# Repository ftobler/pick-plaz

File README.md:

# pick-plaz
Open source pick and place machine

[CAD Onshape](https://cad.onshape.com/documents/175bb45940c329c46a77df39/w/56e16a8885c2fef63520b9e2/e/e7ab10496d879b6cf281b14f)

[STEP file repostory (CAD)](https://github.com/ftobler/pick-plaz-cad)

[More Pictures (Imgur)](https://imgur.com/a/lOQ79OQ)

## Issues

* Part preview missing zero point of ICs

# Wishlist

* Camera sharpen menu in UI (laplacian of camera image)

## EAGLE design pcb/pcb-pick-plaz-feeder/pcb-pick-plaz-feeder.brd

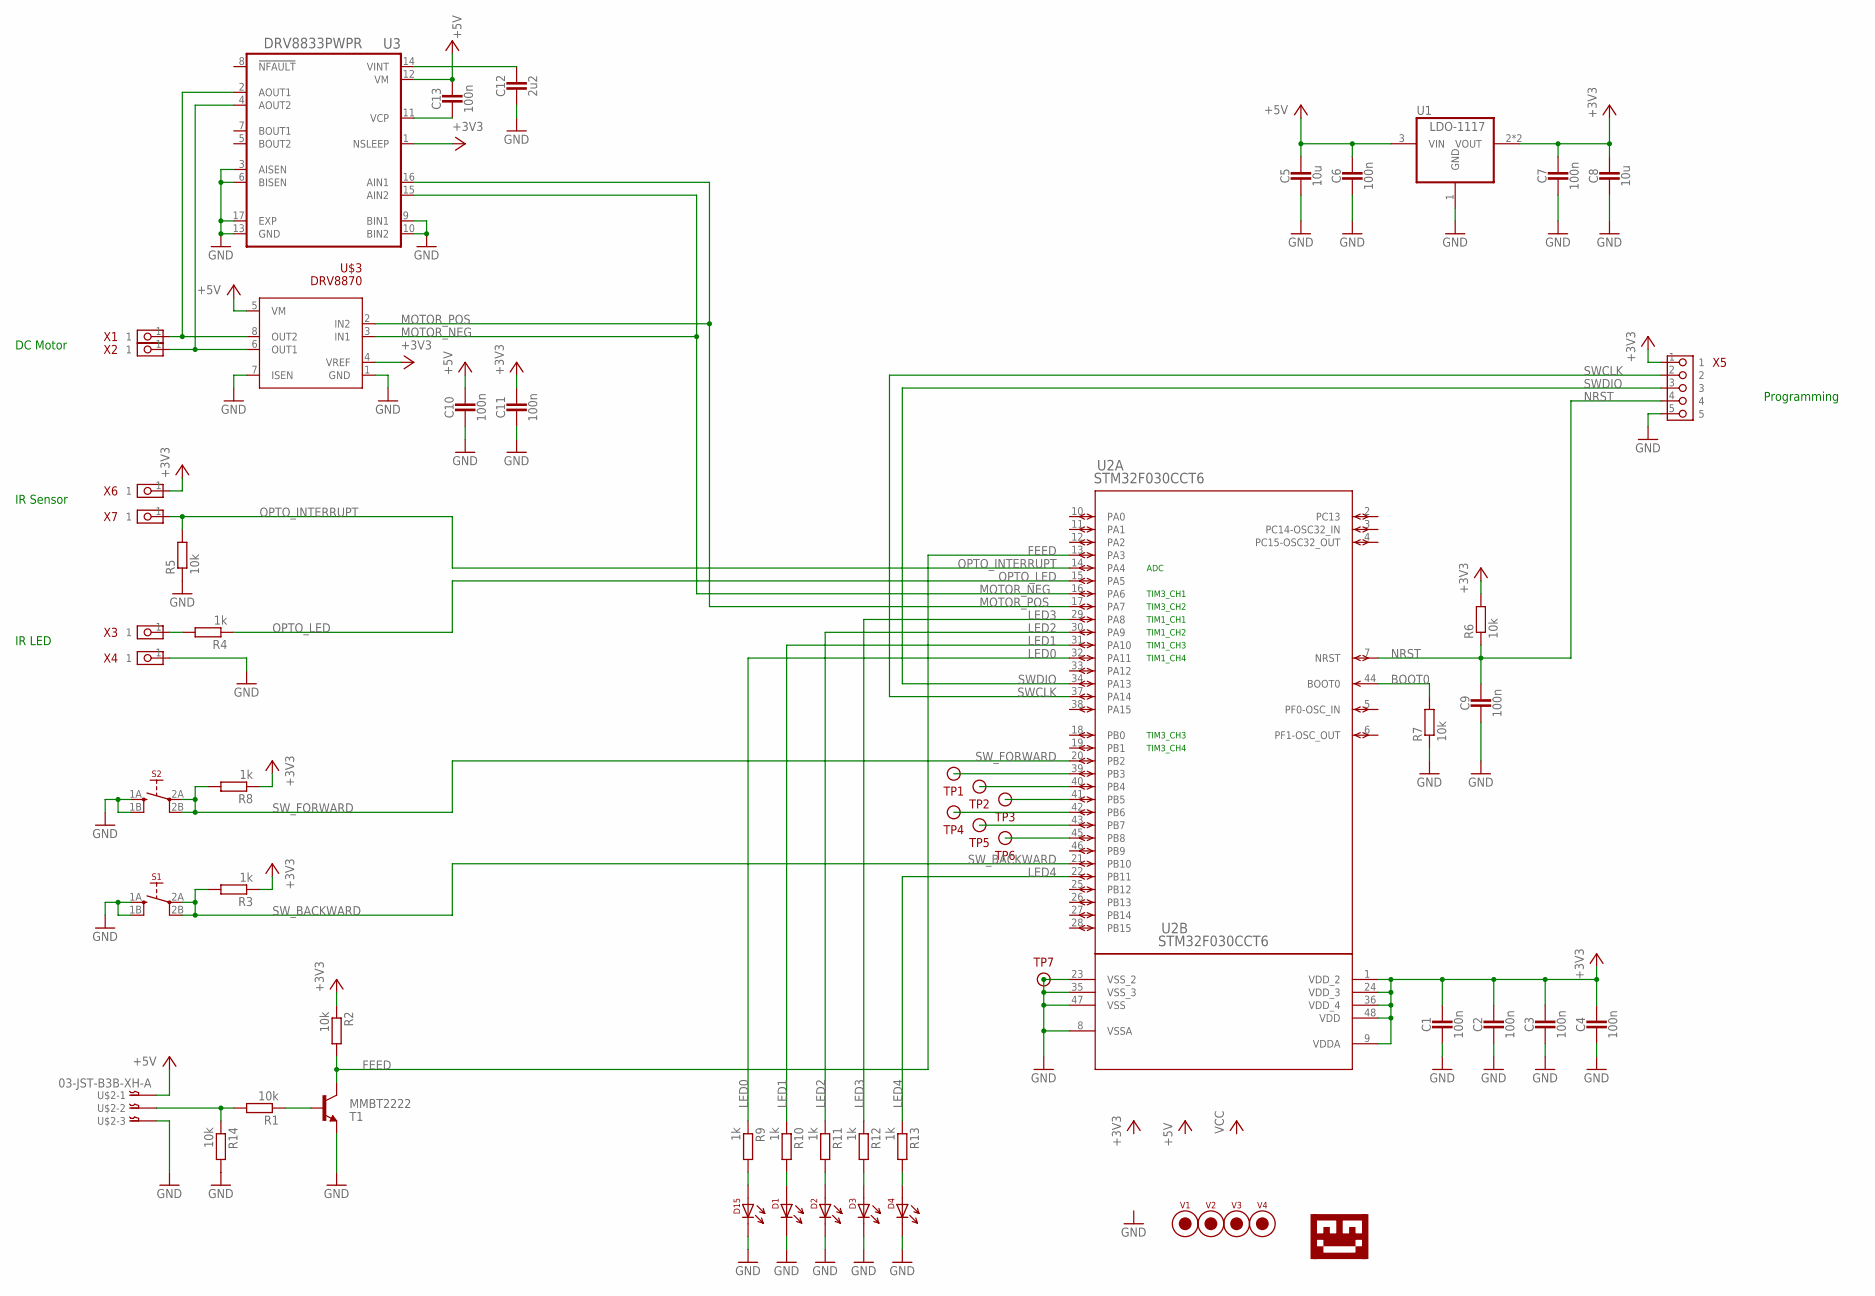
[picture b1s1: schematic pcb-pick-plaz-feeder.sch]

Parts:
C1, C2, C3, C4, C6, C7, C9, C10, C11, C13: 100n; 0603_CAP
C5, C8: 10u; 0805_CAP
C12: 2u2; 0805_CAP
D1, D2, D3, D4, D15: LED-0805; 0805-DOT
R1, R2, R5, R6, R7, R14: 10k; 0603-RES
R3, R4, R8, R9, R10, R11, R12, R13: 1k; 0603-RES
S1, S2: SWITCH_2PD; SWITCH_WH
T1: MMBT2222; SOT23-BEC
TP1, TP2, TP3, TP4, TP5, TP6, TP7: TESTPIN; PIN-SMD-1X1-TEST_1M5
U1: LDO-1117; SOT-89
U2: STM32F030CCT6; LQFP48-7X7MM
U3: DRV8833PWPR; IC_DRV8833PWPR
U$1: LOGO-TOBENG-1MM-FINISH; TOBENG-1MM-FINISH
U$2: 03-JST-B3B-XH-A; B3B-XH
U$3: DRV8870; SOIC-8
V1, V2, V3, V4: FIDUCIAL2MM; FIDUCIAL_2MM
X1, X2, X3, X4, X6, X7: PIN_1X1SMD_BIG_L; PIN_1X1_SMD_BIG_L
X5: PIN_5X1HD; PIN_5X1_HD

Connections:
+3V3: C1.1, C2.1, C3.1, C4.1, C7.1, C8.P$1 (1), C11.1, R2.1, R3.1, R6.2, R8.1, U1.2 (VOUT), U1.2@1 (VOUT), U2.1 (VDD_2), U2.9 (VDDA), U2.24 (VDD_3), U2.36 (VDD_4), U2.48 (VDD), U3.1 (NSLEEP), U$3.4 (VREF), X5.1, X6.1
+5V: C5.P$1 (1), C6.1, C10.1, C13.1, U1.3 (VIN), U3.12 (VM), U$2.P$1, U$3.5 (VM)
BOOT0: R7.2, U2.44 (BOOT0)
FEED: R2.2, T1.C, U2.13 (PA3)
GND: C1.2, C2.2, C3.2, C4.2, C5.P$2 (2), C6.2, C7.2, C8.P$2 (2), C9.2, C10.2, C11.2, C12.P$2 (2), D1.2, D2.2, D3.2, D4.2, D15.2, R5.1, R7.1, R14.2, S1.1A (1), S1.1B (2), S2.1A (1), S2.1B (2), T1.E, TP7.1, U1.1 (GND), U2.8 (VSSA), U2.23 (VSS_2), U2.35 (VSS_3), U2.47 (VSS), U3.3 (AISEN), U3.6 (BISEN), U3.9 (BIN1), U3.10 (BIN2), U3.13 (GND), U3.17 (EXP), U$2.P$3, U$3.1 (GND), U$3.7 (ISEN), X4.1, X5.5
LED0: R9.1, U2.32 (PA11)
LED1: R10.1, U2.31 (PA10)
LED2: R11.1, U2.30 (PA9)
LED3: R12.1, U2.29 (PA8)
LED4: R13.1, U2.22 (PB11)
MOTOR_NEG: U2.16 (PA6), U3.15 (AIN2), U$3.3 (IN1)
MOTOR_POS: U2.17 (PA7), U3.16 (AIN1), U$3.2 (IN2)
unnamed: U3.4 (AOUT2), U$3.6 (OUT1), X2.1
unnamed: U3.2 (AOUT1), U$3.8 (OUT2), X1.1
unnamed: R1.2, R14.1, U$2.P$2
unnamed: R1.1, T1.B
unnamed: R4.2, X3.1
unnamed: D15.1, R9.2
unnamed: D1.1, R10.2
unnamed: D2.1, R11.2
unnamed: D3.1, R12.2
unnamed: D4.1, R13.2
unnamed: TP1.1, U2.39 (PB3)
unnamed: TP2.1, U2.40 (PB4)
unnamed: TP3.1, U2.41 (PB5)
unnamed: TP4.1, U2.42 (PB6)
unnamed: TP5.1, U2.43 (PB7)
unnamed: TP6.1, U2.45 (PB8)
unnamed: C12.P$1 (1), U3.14 (VINT)
unnamed: C13.2, U3.11 (VCP)
NRST: C9.1, R6.1, U2.7 (NRST), X5.4
OPTO_INTERRUPT: R5.2, U2.14 (PA4), X7.1
OPTO_LED: R4.1, U2.15 (PA5)
SWCLK: U2.37 (PA14), X5.2
SWDIO: U2.34 (PA13), X5.3
SW_BACKWARD: R3.2, S1.2A (3), S1.2B (4), U2.21 (PB10)
SW_FORWARD: R8.2, S2.2A (3), S2.2B (4), U2.20 (PB2)

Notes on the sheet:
Programming
DC Motor
IR LED
IR Sensor
ADC
TIM1_CH1
TIM1_CH2
TIM3_CH1
TIM3_CH2
TIM3_CH3
TIM3_CH4
TIM1_CH3
TIM1_CH4

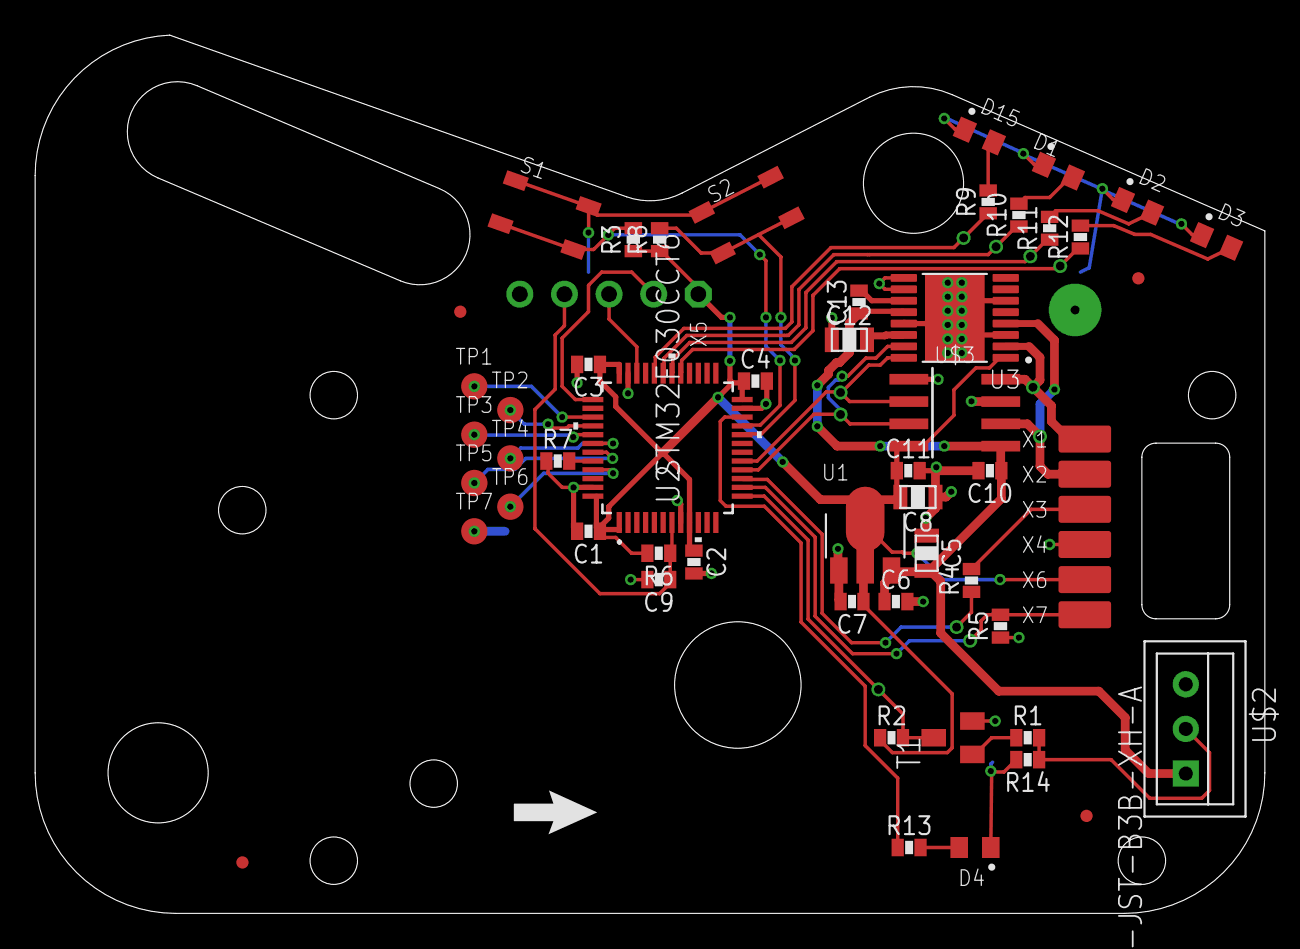
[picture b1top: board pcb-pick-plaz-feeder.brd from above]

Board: 2 copper layers, 70.0 x 50.0 mm, 59 parts (0 on the bottom side), 37 nets.

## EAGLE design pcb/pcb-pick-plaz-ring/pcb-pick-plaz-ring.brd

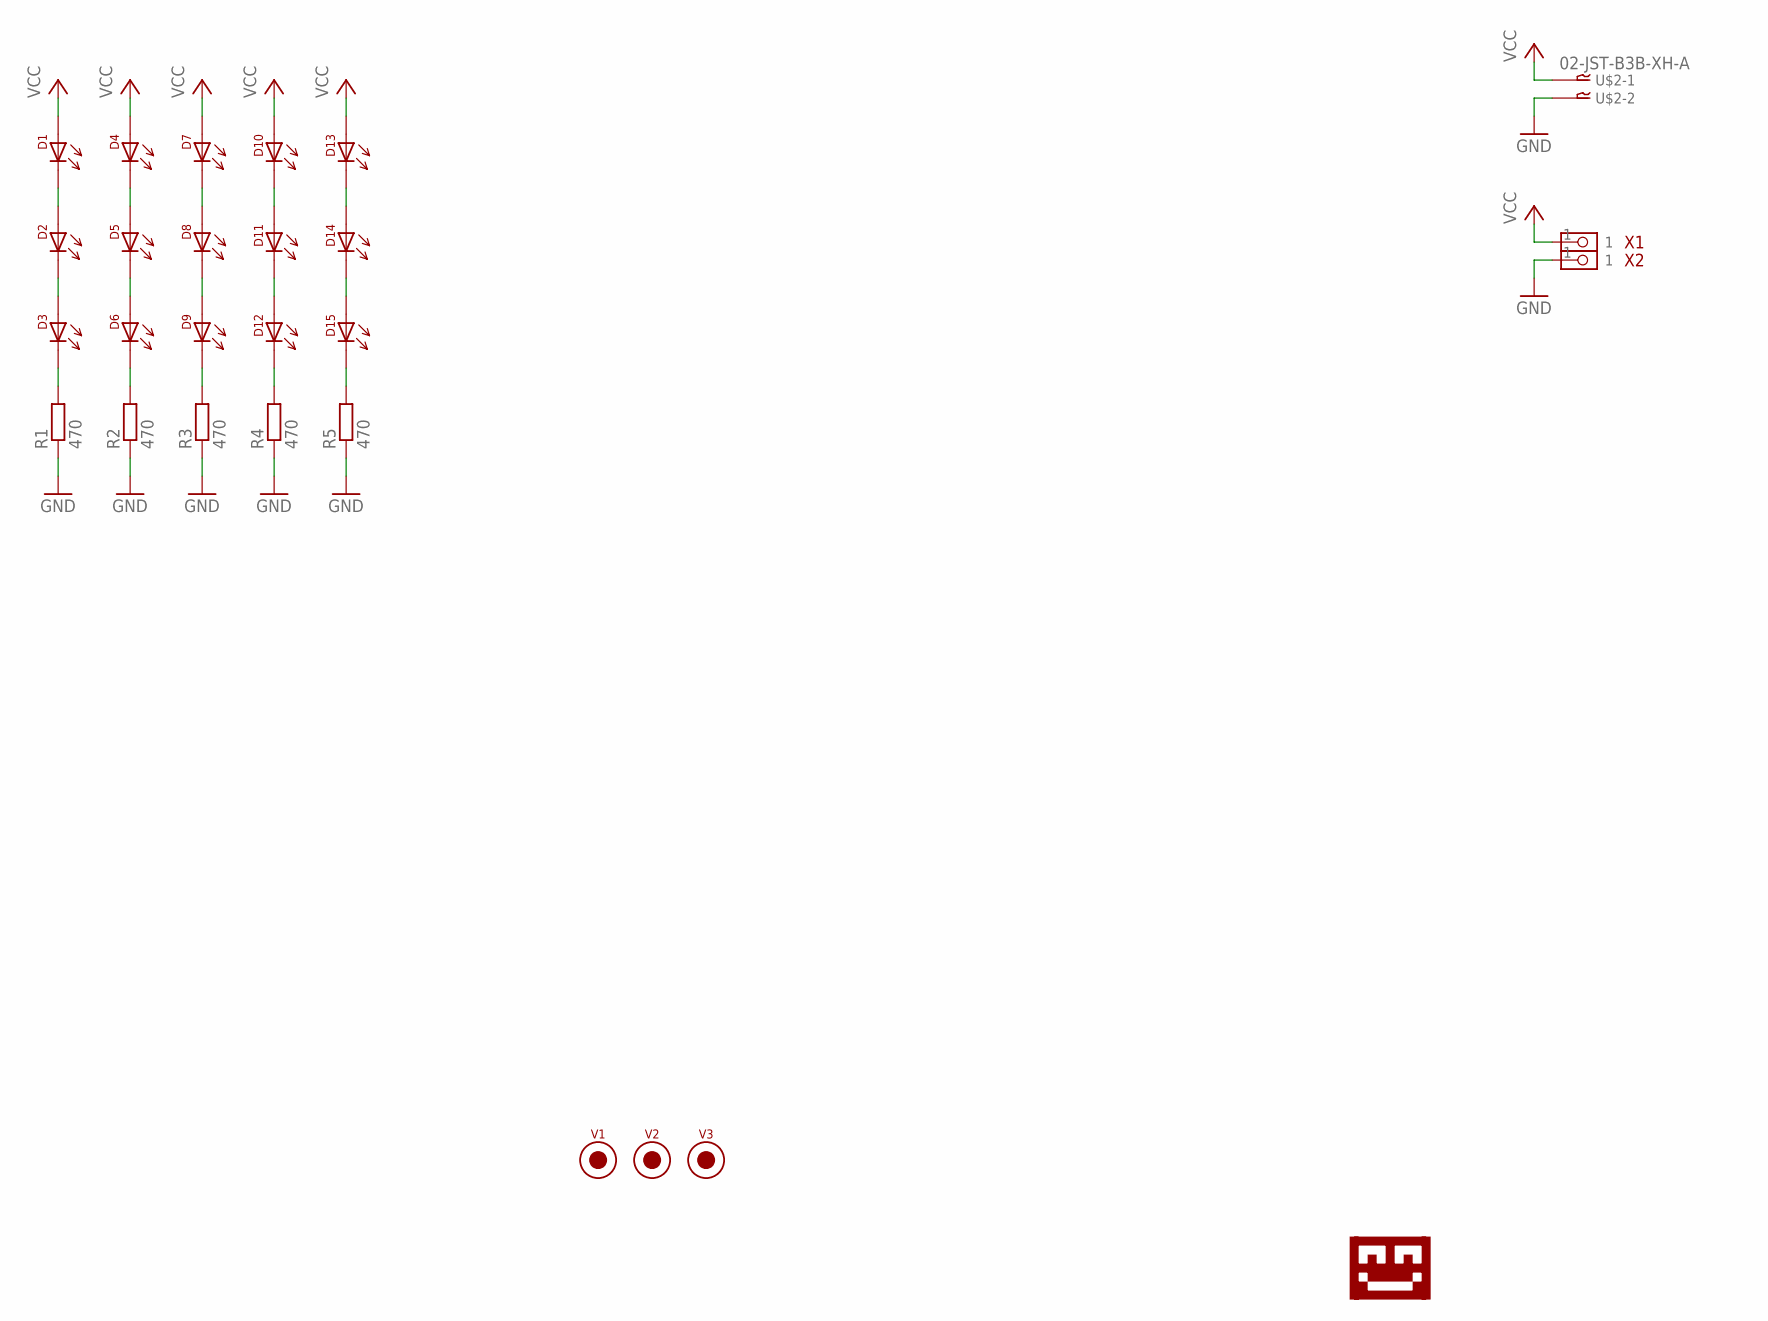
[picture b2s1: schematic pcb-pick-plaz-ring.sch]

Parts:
D1, D2, D3, D4, D5, D6, D7, D8, D9, D10, D11, D12, D13, D14, D15: LED-5730; 5730-LED
R1, R2, R3, R4, R5: 470; 0805_RES
U$1: LOGO-TOBENG-1MM-FINISH; TOBENG-1MM-FINISH
U$2: 02-JST-B3B-XH-A; B2B-XH
V1, V2, V3: FIDUCIAL2MM; FIDUCIAL_2MM
X1, X2: PIN_1X1SMD_BIG_L; PIN_1X1_SMD_BIG_L

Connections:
GND: R1.1, R2.1, R3.1, R4.1, R5.1, U$2.P$2, X2.1
unnamed: D1.C (2), D2.A1 (1), D2.A2 (1)
unnamed: D2.C (2), D3.A1 (1), D3.A2 (1)
unnamed: D3.C (2), R1.2
unnamed: D4.C (2), D5.A1 (1), D5.A2 (1)
unnamed: D5.C (2), D6.A1 (1), D6.A2 (1)
unnamed: D6.C (2), R2.2
unnamed: D7.C (2), D8.A1 (1), D8.A2 (1)
unnamed: D8.C (2), D9.A1 (1), D9.A2 (1)
unnamed: D9.C (2), R3.2
unnamed: D10.C (2), D11.A1 (1), D11.A2 (1)
unnamed: D11.C (2), D12.A1 (1), D12.A2 (1)
unnamed: D12.C (2), R4.2
unnamed: D13.C (2), D14.A1 (1), D14.A2 (1)
unnamed: D14.C (2), D15.A1 (1), D15.A2 (1)
unnamed: D15.C (2), R5.2
VCC: D1.A1 (1), D1.A2 (1), D4.A1 (1), D4.A2 (1), D7.A1 (1), D7.A2 (1), D10.A1 (1), D10.A2 (1), D13.A1 (1), D13.A2 (1), U$2.P$1, X1.1

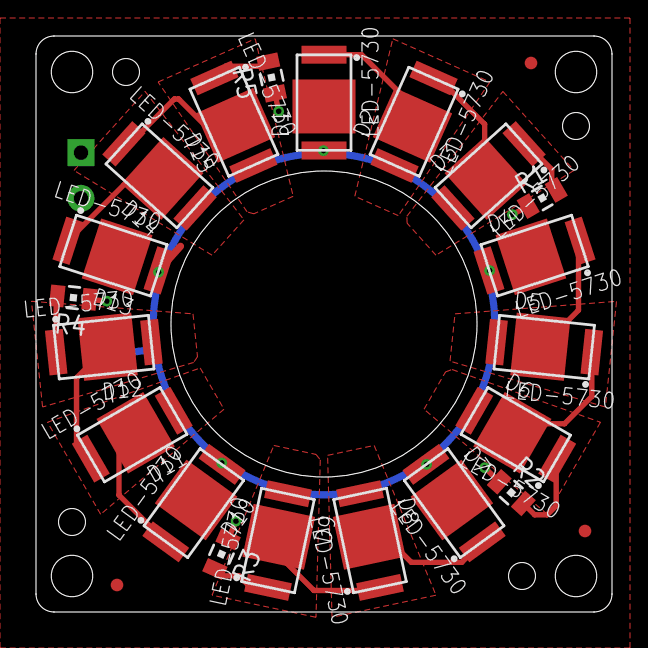
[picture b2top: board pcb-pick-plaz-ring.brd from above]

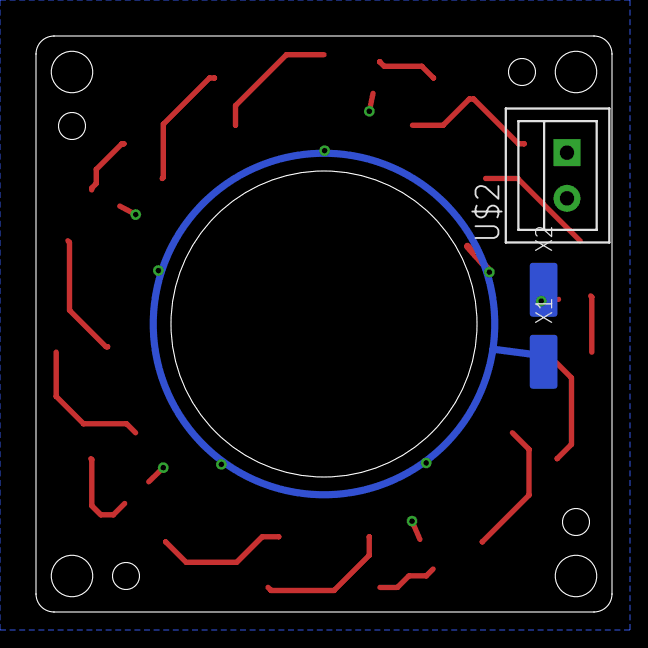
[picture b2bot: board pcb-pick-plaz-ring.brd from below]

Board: 2 copper layers, 32.0 x 32.0 mm, 27 parts (4 on the bottom side), 17 nets.

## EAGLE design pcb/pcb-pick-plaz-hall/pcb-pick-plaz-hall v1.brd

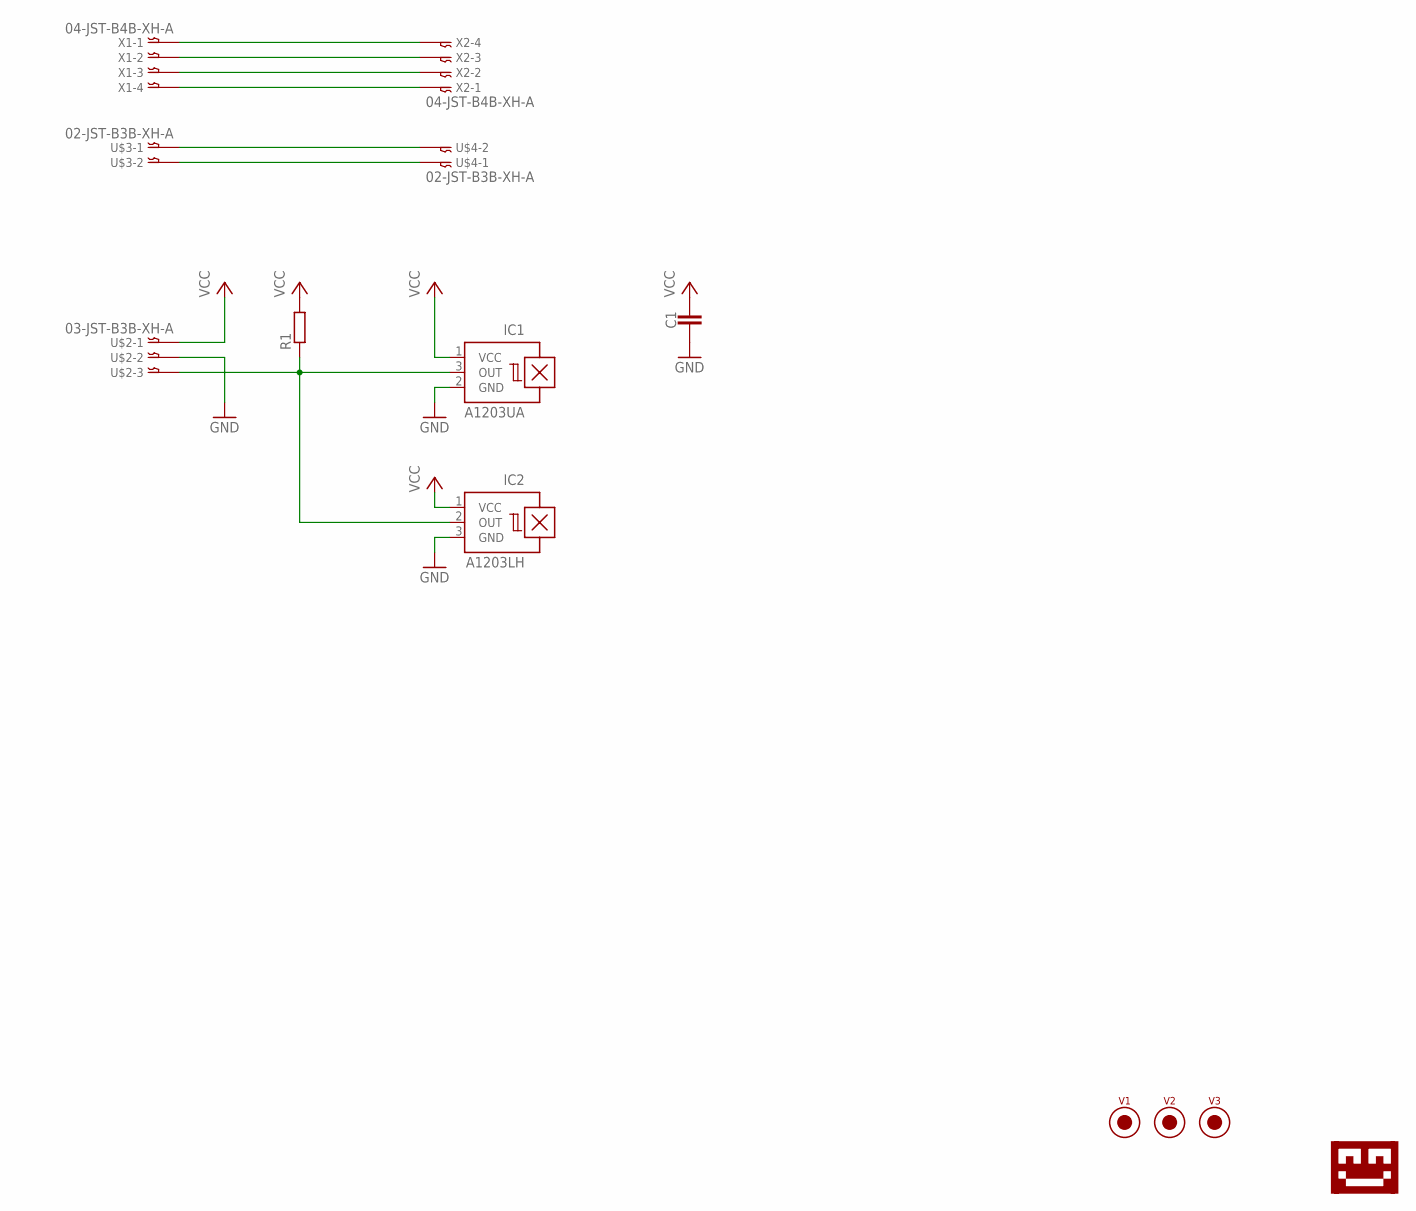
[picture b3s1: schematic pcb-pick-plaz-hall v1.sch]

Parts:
C1: CAPACITOR0603_CAP; 0603_CAP
IC1: A1203UA; SIP3-UA
IC2: A1203LH; SOT23-W
R1: RESISTOR0603_RES; 0603-RES
U$1: LOGO-TOBENG-1MM; TOBENG-1MM
U$2: 03-JST-B3B-XH-A; B3B-XH
U$3, U$4: 02-JST-B3B-XH-A; B2B-XH
V1, V2, V3: FIDUCIAL2MM; FIDUCIAL_2MM
X1, X2: 04-JST-B4B-XH-A; B4B-XH

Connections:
GND: C1.2, IC1.2 (GND), IC2.3 (GND), U$2.P$2
unnamed: X1.P$1, X2.P$4
unnamed: X1.P$2, X2.P$3
unnamed: X1.P$3, X2.P$2
unnamed: X1.P$4, X2.P$1
unnamed: U$3.P$1, U$4.P$2
unnamed: U$3.P$2, U$4.P$1
unnamed: IC1.3 (OUT), IC2.2 (OUT), R1.1, U$2.P$3
VCC: C1.1, IC1.1 (VCC), IC2.1 (VCC), R1.2, U$2.P$1

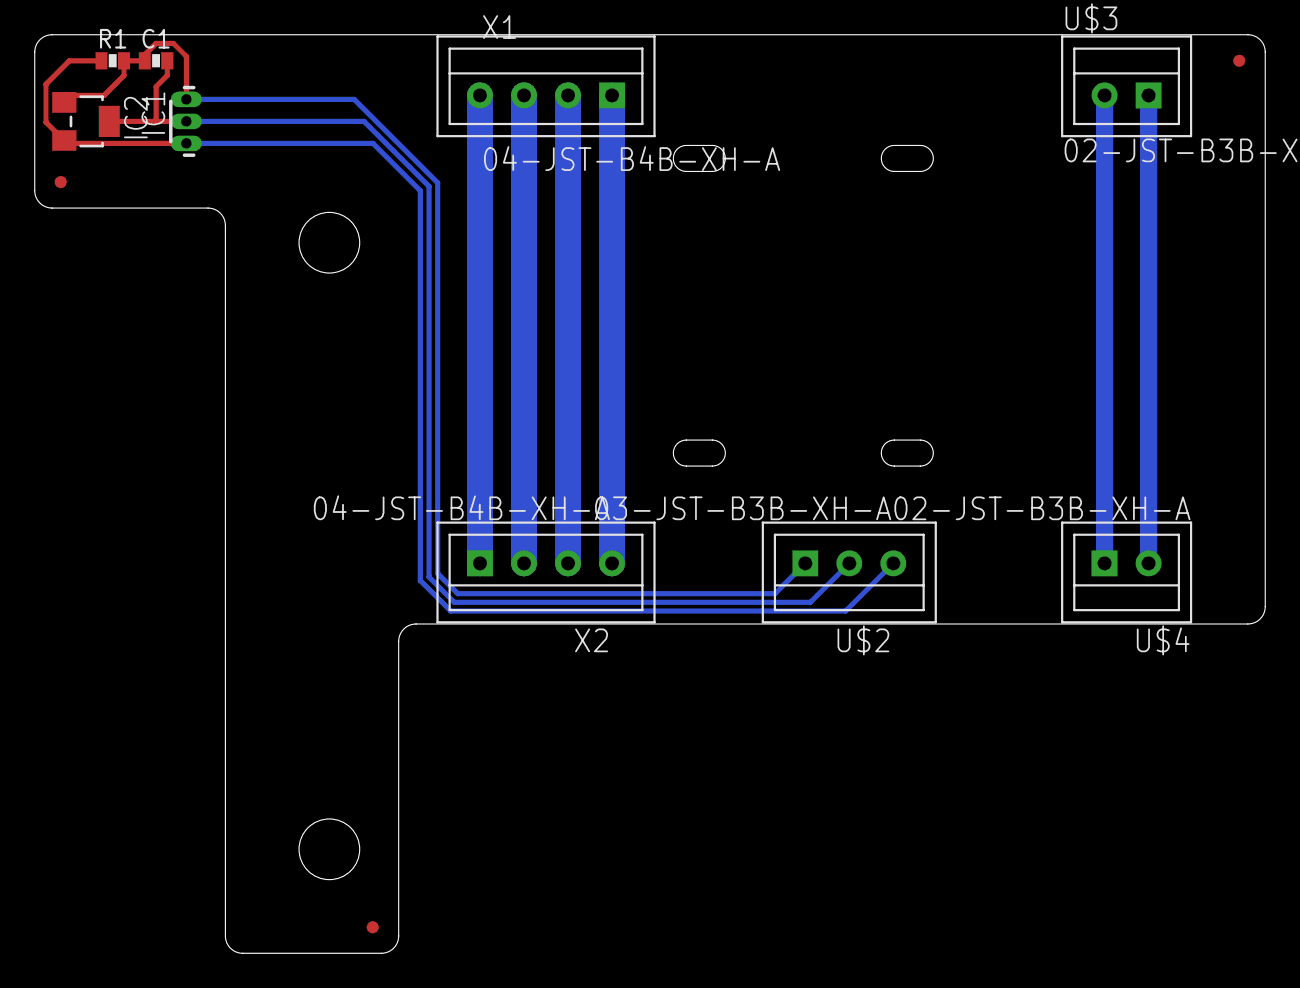
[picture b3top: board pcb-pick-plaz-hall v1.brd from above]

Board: 2 copper layers, 71.0 x 53.0 mm, 13 parts (1 on the bottom side), 9 nets.

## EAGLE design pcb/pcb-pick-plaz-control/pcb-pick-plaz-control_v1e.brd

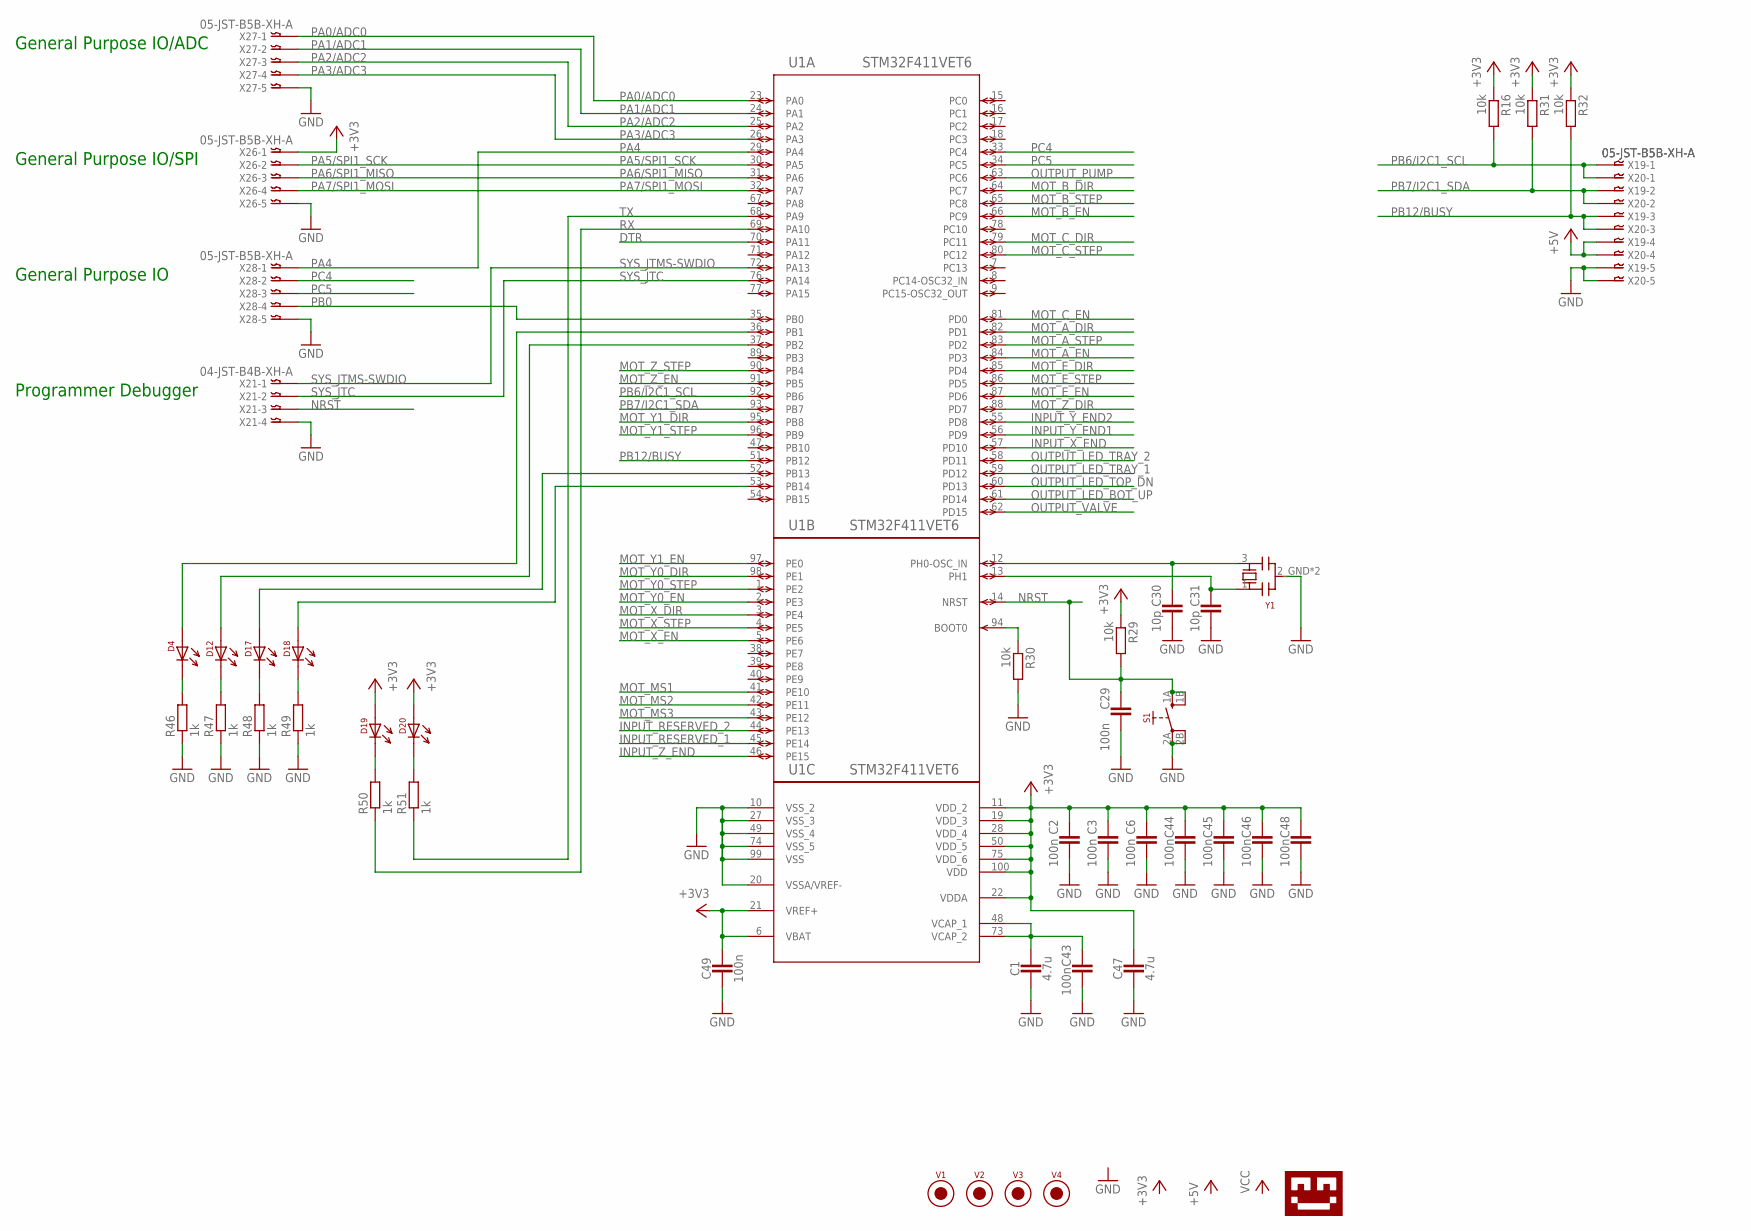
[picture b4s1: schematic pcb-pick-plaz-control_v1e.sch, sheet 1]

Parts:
C1, C47: 4.7u; 0805_CAP
C2, C3, C6, C29, C43, C44, C45, C46, C48, C49: 100n; 0603_CAP
C30, C31: 10p; 0603_CAP
D4, D12, D17, D18, D19, D20: LED-0805; 0805-DOT
R16, R29, R30, R31, R32: 10k; 0603-RES
R46, R47, R48, R49, R50, R51: 1k; 0603-RES
S1: SWITCH_2PD; SWITCH_WH
U1: STM32F411VET6; LQFP100-14X14MM
U$1: LOGO-TOBENG-1MM-FINISH; TOBENG-1MM-FINISH
V1, V2, V3, V4: FIDUCIAL2MM; FIDUCIAL_2MM
X19, X20, X26, X27, X28: 05-JST-B5B-XH-A; B5B-XH
X21: 04-JST-B4B-XH-A; B4B-XH
Y1: 3213-QUARZ3225; 3225-QUARZ

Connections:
+3V3: C2.1, C3.1, C6.1, C44.1, C45.1, C46.1, C47.P$1 (1), C48.1, C49.1, D19.1, D20.1, R16.1, R29.1, R31.1, R32.1, U1.6 (VBAT), U1.11 (VDD_2), U1.19 (VDD_3), U1.21 (VREF+), U1.22 (VDDA), U1.28 (VDD_4), U1.50 (VDD_5), U1.75 (VDD_6), U1.100 (VDD), X26.P$1; also elsewhere on the board
+5V: X19.P$4, X20.P$4; also elsewhere on the board
DTR: U1.70 (PA11); also elsewhere on the board
GND: C1.P$2 (2), C2.2, C3.2, C6.2, C29.2, C30.2, C31.2, C43.2, C44.2, C45.2, C46.2, C47.P$2 (2), C48.2, C49.2, R30.2, R46.1, R47.1, R48.1, R49.1, S1.2A (3), S1.2B (4), U1.10 (VSS_2), U1.20 (VSSA/VREF-), U1.27 (VSS_3), U1.49 (VSS_4), U1.74 (VSS_5), U1.99 (VSS), X19.P$5, X20.P$5, X21.P$4, X26.P$5, X27.P$5, X28.P$5, Y1.2_GND (2), Y1.4_GND (2); also elsewhere on the board
INPUT_RESERVED_1: U1.45 (PE14); also elsewhere on the board
INPUT_RESERVED_2: U1.44 (PE13); also elsewhere on the board
INPUT_X_END: U1.57 (PD10); also elsewhere on the board
INPUT_Y_END1: U1.56 (PD9); also elsewhere on the board
INPUT_Y_END2: U1.55 (PD8); also elsewhere on the board
INPUT_Z_END: U1.46 (PE15); also elsewhere on the board
MOT_A_DIR: U1.82 (PD1); also elsewhere on the board
MOT_A_EN: U1.84 (PD3); also elsewhere on the board
MOT_A_STEP: U1.83 (PD2); also elsewhere on the board
MOT_B_DIR: U1.64 (PC7); also elsewhere on the board
MOT_B_EN: U1.66 (PC9); also elsewhere on the board
MOT_B_STEP: U1.65 (PC8); also elsewhere on the board
MOT_C_DIR: U1.79 (PC11); also elsewhere on the board
MOT_C_EN: U1.81 (PD0); also elsewhere on the board
MOT_C_STEP: U1.80 (PC12); also elsewhere on the board
MOT_E_DIR: U1.85 (PD4); also elsewhere on the board
MOT_E_EN: U1.87 (PD6); also elsewhere on the board
MOT_E_STEP: U1.86 (PD5); also elsewhere on the board
MOT_MS1: U1.41 (PE10); also elsewhere on the board
MOT_MS2: U1.42 (PE11); also elsewhere on the board
MOT_MS3: U1.43 (PE12); also elsewhere on the board
MOT_X_DIR: U1.3 (PE4); also elsewhere on the board
MOT_X_EN: U1.5 (PE6); also elsewhere on the board
MOT_X_STEP: U1.4 (PE5); also elsewhere on the board
MOT_Y0_DIR: U1.98 (PE1); also elsewhere on the board
MOT_Y0_EN: U1.2 (PE3); also elsewhere on the board
MOT_Y0_STEP: U1.1 (PE2); also elsewhere on the board
MOT_Y1_DIR: U1.95 (PB8); also elsewhere on the board
MOT_Y1_EN: U1.97 (PE0); also elsewhere on the board
MOT_Y1_STEP: U1.96 (PB9); also elsewhere on the board
MOT_Z_DIR: U1.88 (PD7); also elsewhere on the board
MOT_Z_EN: U1.91 (PB5); also elsewhere on the board
MOT_Z_STEP: U1.90 (PB4); also elsewhere on the board
unnamed: R30.1, U1.94 (BOOT0)
unnamed: C1.P$1 (1), C43.1, U1.48 (VCAP_1), U1.73 (VCAP_2)
unnamed: D4.2, R46.2
unnamed: D12.2, R47.2
unnamed: D17.2, R48.2
unnamed: D18.2, R49.2
unnamed: D18.1, U1.53 (PB14)
unnamed: D17.1, U1.52 (PB13)
unnamed: C30.1, U1.12 (PH0-OSC_IN), Y1.3
unnamed: C31.1, U1.13 (PH1), Y1.1
unnamed: D12.1, U1.37 (PB2)
unnamed: D4.1, U1.36 (PB1)
unnamed: D19.2, R50.2
unnamed: D20.2, R51.2
NRST: C29.1, R29.2, S1.1A (1), S1.1B (2), U1.14 (NRST), X21.P$3
OUTPUT_LED_BOT_UP: U1.61 (PD14); also elsewhere on the board
OUTPUT_LED_TOP_DN: U1.60 (PD13); also elsewhere on the board
OUTPUT_LED_TRAY_1: U1.59 (PD12); also elsewhere on the board
OUTPUT_LED_TRAY_2: U1.58 (PD11); also elsewhere on the board
OUTPUT_PUMP: U1.63 (PC6); also elsewhere on the board
OUTPUT_VALVE: U1.62 (PD15); also elsewhere on the board
PA0/ADC0: U1.23 (PA0), X27.P$1
PA1/ADC1: U1.24 (PA1), X27.P$2
PA2/ADC2: U1.25 (PA2), X27.P$3
PA3/ADC3: U1.26 (PA3), X27.P$4
PA4: U1.29 (PA4), X28.P$1
PA5/SPI1_SCK: U1.30 (PA5), X26.P$2
PA6/SPI1_MISO: U1.31 (PA6), X26.P$3
PA7/SPI1_MOSI: U1.32 (PA7), X26.P$4
PB0: U1.35 (PB0), X28.P$4
PB6/I2C1_SCL: R16.2, U1.92 (PB6), X19.P$1, X20.P$1
PB7/I2C1_SDA: R31.2, U1.93 (PB7), X19.P$2, X20.P$2
PB12/BUSY: R32.2, U1.51 (PB12), X19.P$3, X20.P$3
PC4: U1.33 (PC4), X28.P$2
PC5: U1.34 (PC5), X28.P$3
RX: R50.1, U1.69 (PA10); also elsewhere on the board
SYS_JTC: U1.76 (PA14), X21.P$2
SYS_JTMS-SWDIO: U1.72 (PA13), X21.P$1
TX: R51.1, U1.68 (PA9); also elsewhere on the board

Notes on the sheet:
General Purpose IO/ADC
General Purpose IO/SPI
Programmer Debugger
General Purpose IO

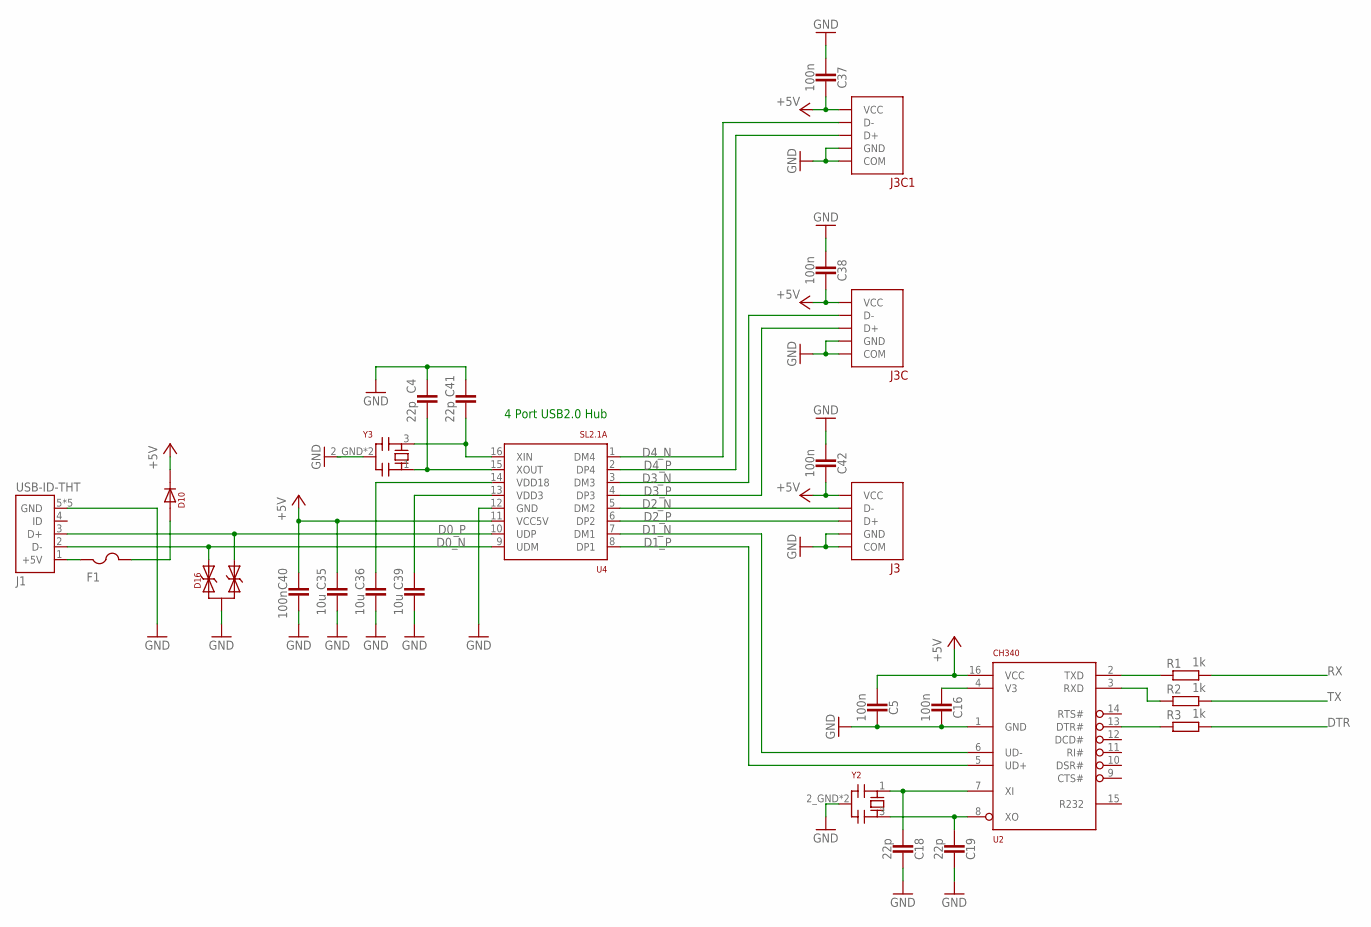
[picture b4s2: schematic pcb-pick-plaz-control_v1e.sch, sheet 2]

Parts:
C4, C18, C19, C41: 22p; 0603_CAP
C5, C16, C37, C38, C40, C42: 100n; 0603_CAP
C35, C36, C39: 10u; 0805_CAP
D10: DIODE-1206; 1206-DOT
D16: DIODE-TVS; SOT-23
F1: PTCFUSE-1206; R1206
J1: USB-ID-THT; USB-MICRO-THT
J3, J3C, J3C1: USB-LCSC_C42431; USB-A-LCSC_C42431
R1, R2, R3: 1k; 0603-RES
U2: CH340; SOIC-16
U4: SL2.1A; SOIC-16
Y2, Y3: 3213-QUARZ3225; 3225-QUARZ

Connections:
+5V: C5.2, C35.P$2 (2), C37.1, C38.1, C40.2, C42.1, D10.2, J3.VCC, J3C.VCC, J3C1.VCC, U2.16 (VCC), U4.11 (VCC5V); also elsewhere on the board
D0_N: D16.2, J1.2 (D-), U4.9 (UDM)
D0_P: D16.1, J1.3 (D+), U4.10 (UDP)
D1_N: U2.6 (UD-), U4.7 (DM1)
D1_P: U2.5 (UD+), U4.8 (DP1)
D2_N: J3.D-, U4.5 (DM2)
D2_P: J3.D+, U4.6 (DP2)
D3_N: J3C.D-, U4.3 (DM3)
D3_P: J3C.D+, U4.4 (DP3)
D4_N: J3C1.D-, U4.1 (DM4)
D4_P: J3C1.D+, U4.2 (DP4)
DTR: R3.2; also elsewhere on the board
GND: C4.2, C5.1, C16.1, C18.1, C19.1, C35.P$1 (1), C36.P$1 (1), C37.2, C38.2, C39.P$1 (1), C40.1, C41.2, C42.2, D16.3, J1.5 (GND), J1.GND1 (GND), J1.GND2 (GND), J1.GND3 (GND), J1.GND4 (GND), J3.COM1 (COM), J3.COM2 (COM), J3.GND, J3C.COM1 (COM), J3C.COM2 (COM), J3C.GND, J3C1.COM1 (COM), J3C1.COM2 (COM), J3C1.GND, U2.1 (GND), U4.12 (GND), Y2.2_GND (2), Y2.4_GND (2), Y3.2_GND (2), Y3.4_GND (2); also elsewhere on the board
unnamed: C18.2, U2.7 (XI), Y2.1
unnamed: C19.2, U2.8 (XO), Y2.3
unnamed: R1.1, U2.2 (TXD)
unnamed: R2.1, U2.3 (RXD)
unnamed: C16.2, U2.4 (V3)
unnamed: C41.1, U4.16 (XIN), Y3.3
unnamed: R3.1, U2.13 (DTR#)
unnamed: C4.1, U4.15 (XOUT), Y3.1
unnamed: C36.P$2 (2), U4.14 (VDD18)
unnamed: C39.P$2 (2), U4.13 (VDD3)
unnamed: D10.1, F1.2
RX: R1.2; also elsewhere on the board
TX: R2.2; also elsewhere on the board
VINUSB: F1.1, J1.1 (+5V)

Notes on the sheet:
4 Port USB2.0 Hub

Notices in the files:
parts and their libraries:
COPYRIGHT: Copyright (C) 2018 Accelerated Designs. All rights reserved
